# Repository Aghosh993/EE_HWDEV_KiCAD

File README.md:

# EE_HWDEV_KiCAD
Repository containing all KiCAD schematic, layout and project files for PCB schematic capture and layout projects

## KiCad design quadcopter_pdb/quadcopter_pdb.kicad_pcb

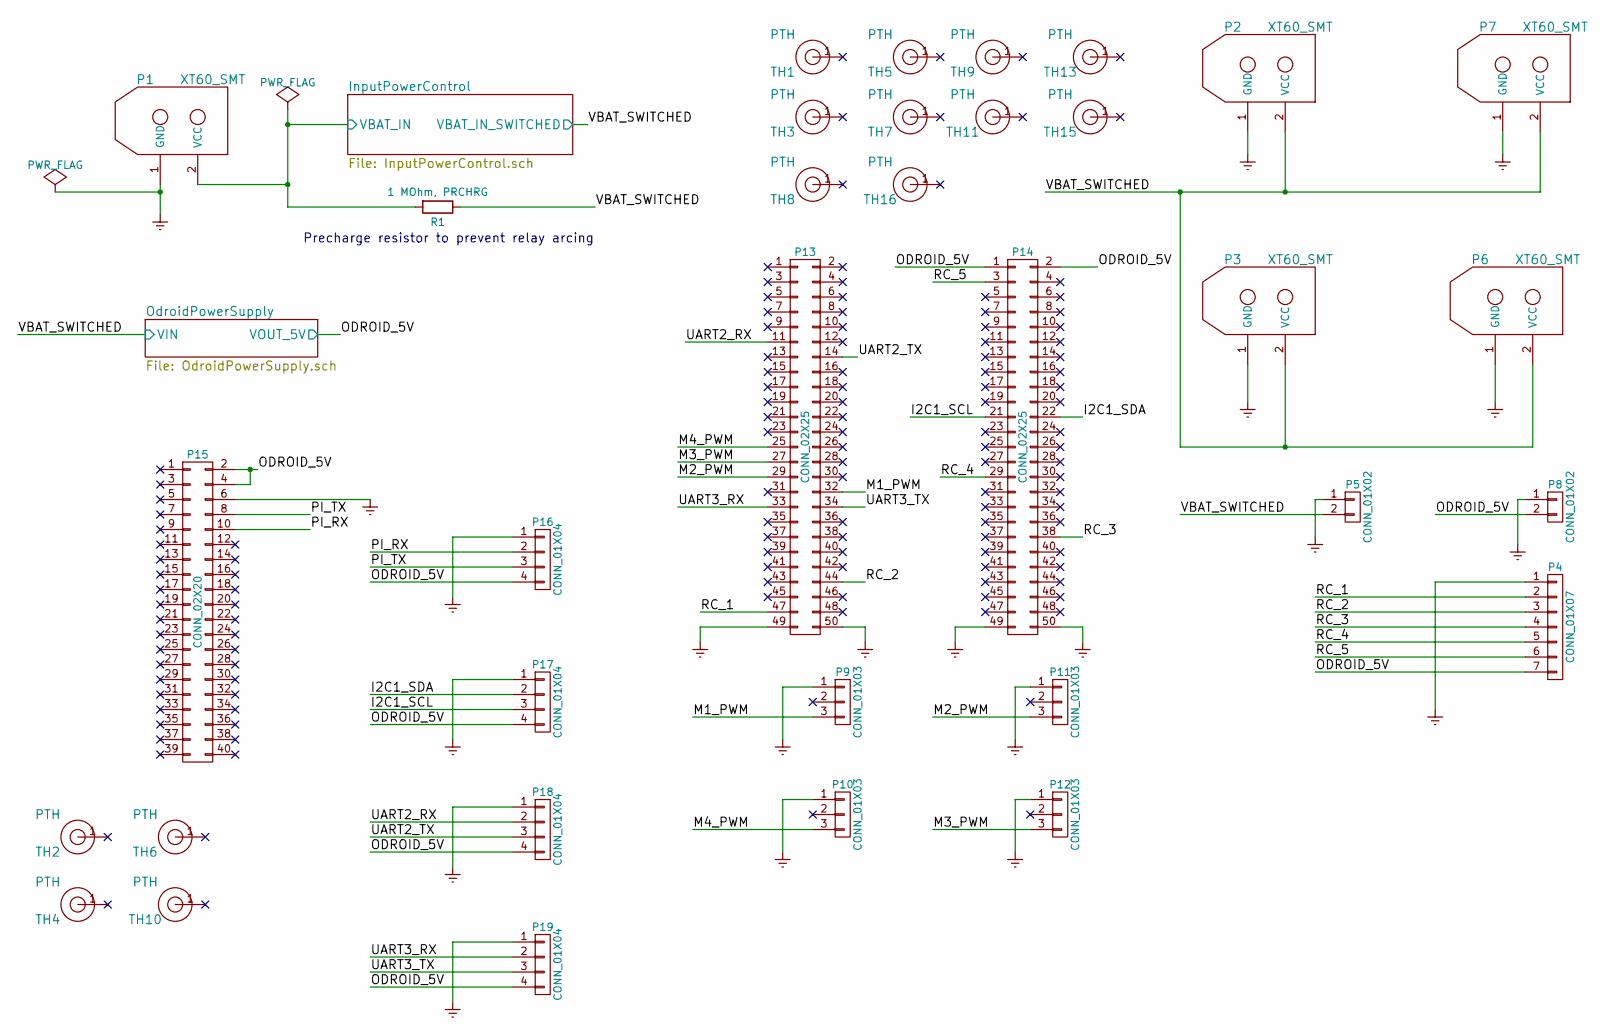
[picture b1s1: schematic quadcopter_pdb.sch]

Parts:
P1, P2, P3, P6, P7: XT60_SMT
P4: CONN_01X07; Pin_Header_Straight_1x07
P5, P8: CONN_01X02; Pin_Header_Angled_1x02
P9, P10, P11, P12: CONN_01X03; Pin_Header_Straight_1x03
P13, P14: CONN_02X25; Pin_Header_Straight_2x25
P15: CONN_02X20; Pin_Header_Straight_2x20
P16, P17, P18, P19: CONN_01X04; Pin_Header_Straight_1x04
R1: 1 MOhm, PRCHRG; R_0402
TH1, TH3, TH5, TH7, TH8, TH9, TH11, TH13, TH15, TH16: PTH
TH2, TH4, TH6, TH10: PTH; MountingHole_3mm

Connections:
/I2C1_SCL: P14.21, P17.3
/I2C1_SDA: P14.22, P17.2
/InputPowerControl/VBAT_IN: P1.2 (VCC), R1.2; also elsewhere on the board
/M1_PWM: P9.3, P13.32
/M2_PWM: P11.3, P13.29
/M3_PWM: P12.3, P13.27
/M4_PWM: P10.3, P13.25
/ODROID_5V: P4.7, P8.2, P14.1, P14.2, P15.2, P15.4, P16.4, P17.4, P18.4, P19.4; also elsewhere on the board
/PI_RX: P15.10, P16.2
/PI_TX: P15.8, P16.3
/RC_1: P4.2, P13.47
/RC_2: P4.3, P13.44
/RC_3: P4.4, P14.38
/RC_4: P4.5, P14.29
/RC_5: P4.6, P14.3
/UART2_RX: P13.11, P18.2
/UART2_TX: P13.14, P18.3
/UART3_RX: P13.33, P19.2
/UART3_TX: P13.34, P19.3
/VBAT_SWITCHED: P2.2 (VCC), P3.2 (VCC), P5.2, P6.2 (VCC), P7.2 (VCC), R1.1; also elsewhere on the board
Earth: P1.1 (GND), P2.1 (GND), P3.1 (GND), P4.1, P5.1, P6.1 (GND), P7.1 (GND), P8.1, P9.1, P10.1, P11.1, P12.1, P13.49, P13.50, P14.49, P14.50, P15.6, P16.1, P17.1, P18.1, P19.1; also elsewhere on the board

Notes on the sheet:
Precharge resistor to prevent relay arcing

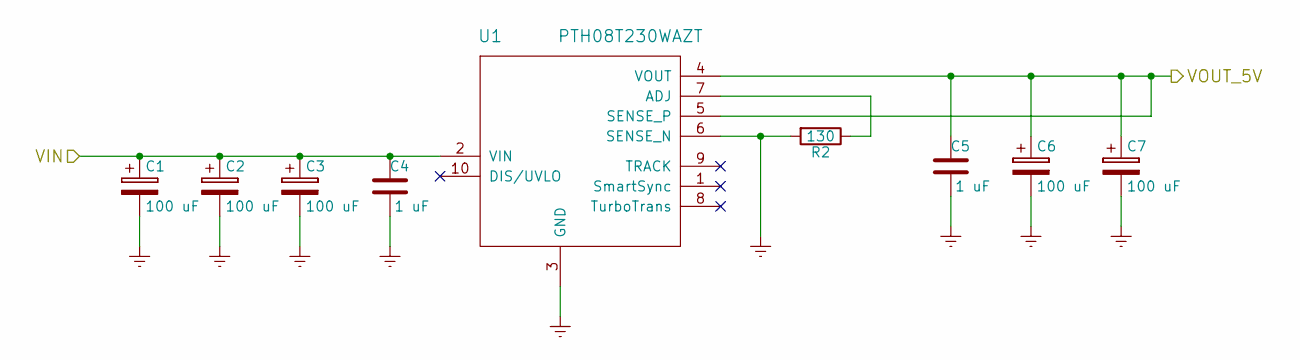
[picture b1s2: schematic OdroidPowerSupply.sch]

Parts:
C1, C2, C3, C6, C7: 100 uF; C_Radial_D6.3_L11.2_P2.5
C4, C5: 1 uF; C_0805_HandSoldering
R2: 130; R_0603_HandSoldering
U1: PTH08T230WAZT; PTH08T230WAZT_BCM

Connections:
/ODROID_5V: C5.2, C6.1, C7.1, U1.4 (VOUT), U1.5 (SENSE_P); also elsewhere on the board
/VBAT_SWITCHED: C1.1, C2.1, C3.1, C4.2, U1.2 (VIN); also elsewhere on the board
Earth: C1.2, C2.2, C3.2, C4.1, C5.1, C6.2, C7.2, R2.2, U1.3 (GND), U1.6 (SENSE_N); also elsewhere on the board
unnamed: R2.1, U1.7 (ADJ)

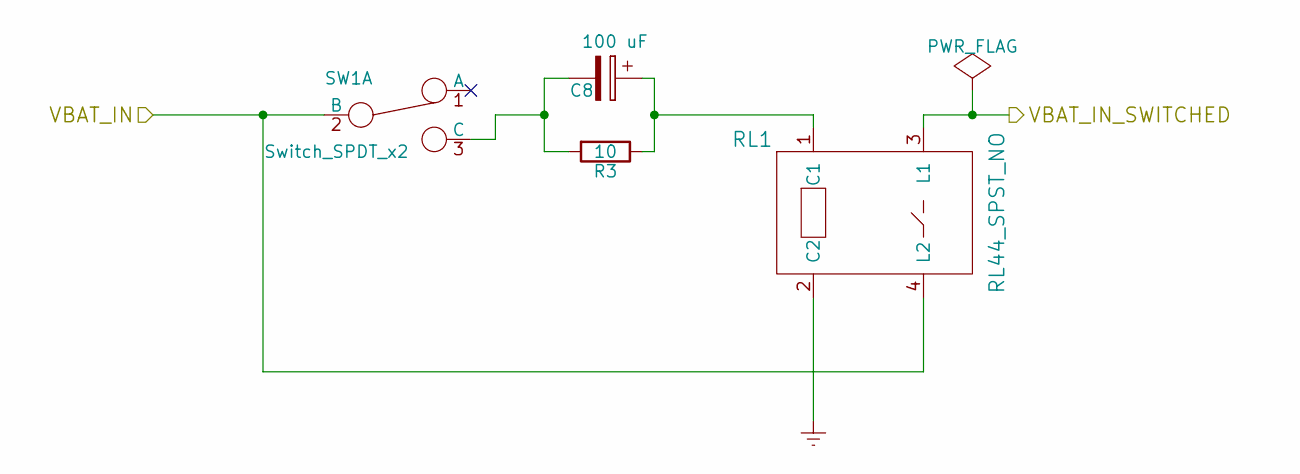
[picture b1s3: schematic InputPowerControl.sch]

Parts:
C8: 100 uF; C_Radial_D6.3_L11.2_P2.5
R3: 10; Resistor_Horizontal_RM10mm
RL1: RL44_SPST_NO; RELAY_RL44
SW1: Switch_SPDT_x2; SW_SPDT_ThroughHole

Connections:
/InputPowerControl/VBAT_IN: RL1.4 (L2), SW1.2 (B); also elsewhere on the board
/VBAT_SWITCHED: RL1.3 (L1); also elsewhere on the board
Earth: RL1.2 (C2); also elsewhere on the board
unnamed: C8.1, R3.1, RL1.1 (C1)
unnamed: C8.2, R3.2, SW1.3 (C)

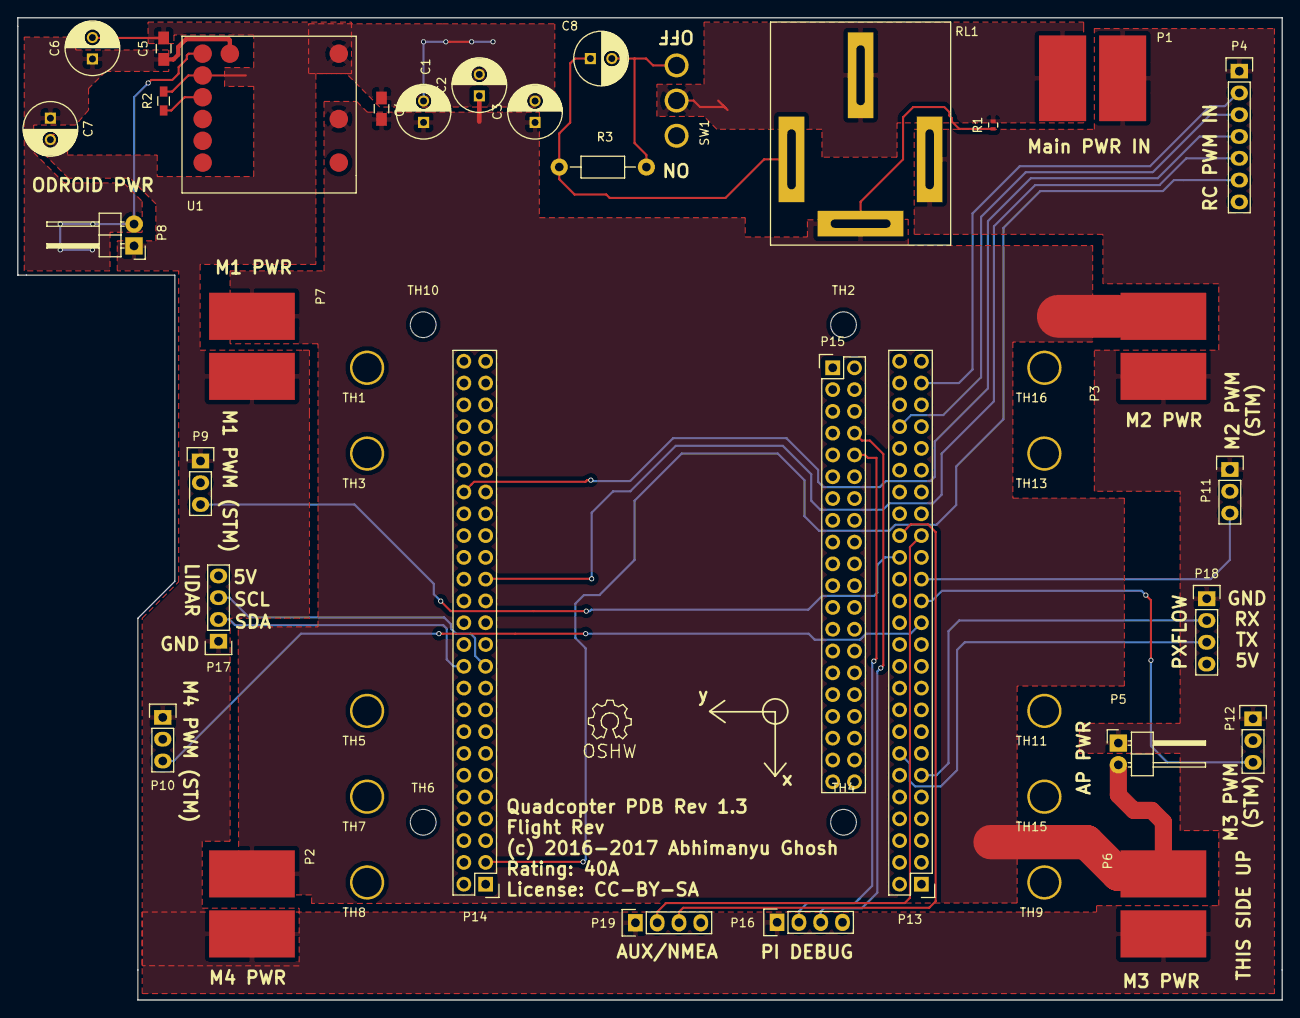
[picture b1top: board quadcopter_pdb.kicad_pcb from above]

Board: 2 copper layers, 147.4 x 114.5 mm, 47 parts (0 on the bottom side), 24 nets.

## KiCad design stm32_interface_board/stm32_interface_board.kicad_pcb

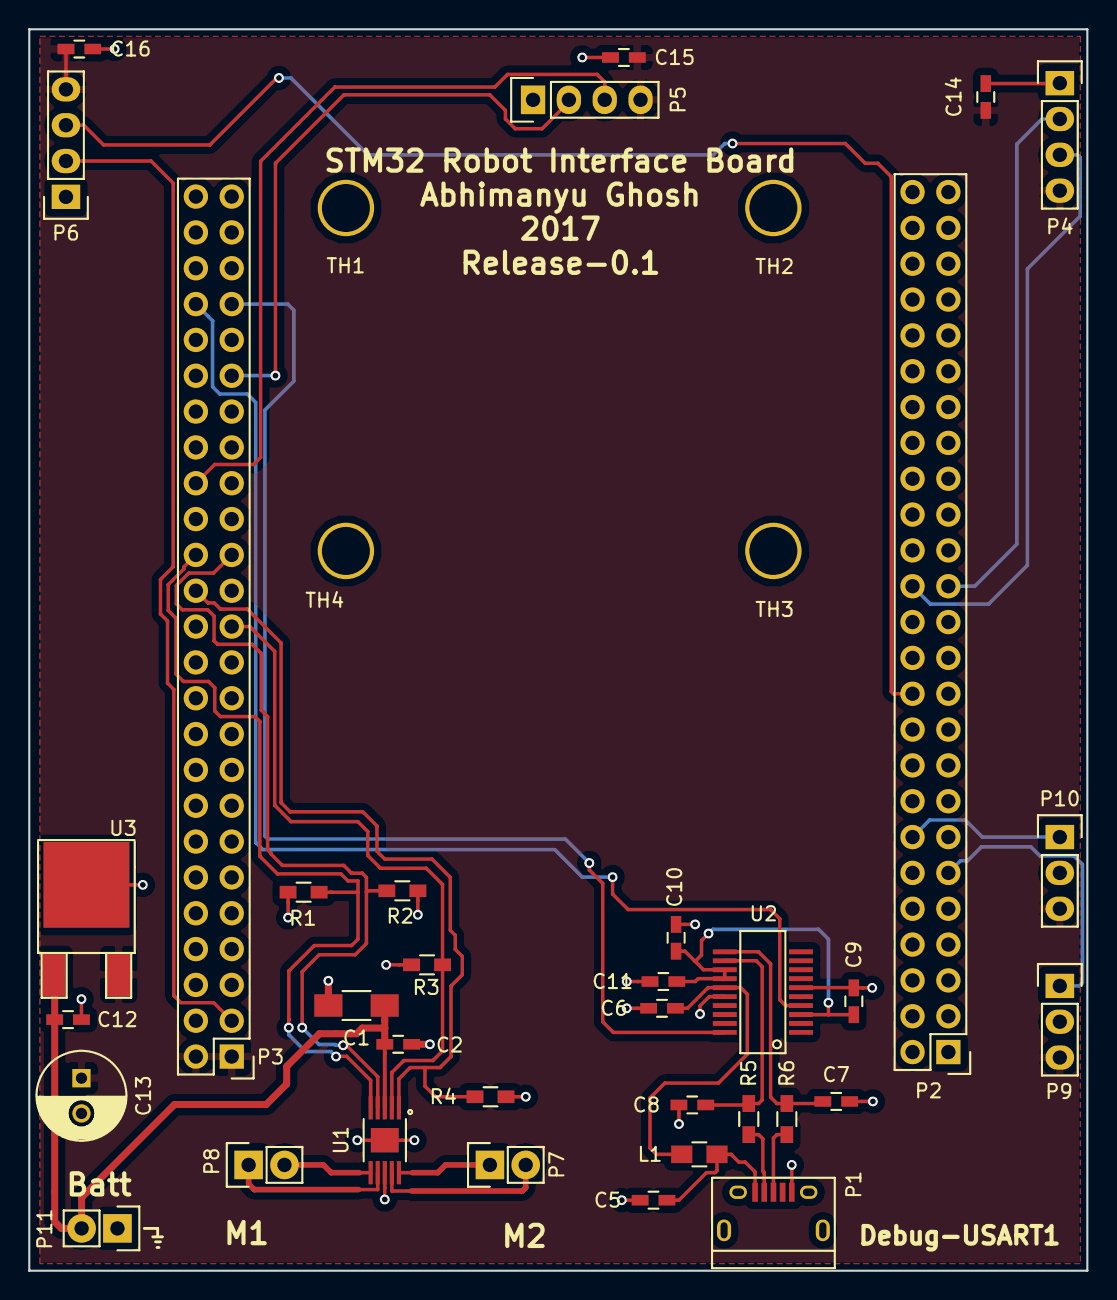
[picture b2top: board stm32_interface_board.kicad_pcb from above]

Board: 2 copper layers, 75.0 x 88.0 mm, 39 parts (0 on the bottom side), 28 nets.

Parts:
C1: 22 uF; C_1206_HandSoldering
C2, C5, C6, C9, C10, C11, C12, C14, C15, C16: 0.1 uF; C_0603_HandSoldering
C7, C8: 47 pF; C_0603_HandSoldering
C13: 2.2 uF; C_Radial_D6.3_L11.2_P2.5
L1: 40-Ohm Ferrite; C_0805_HandSoldering
P1: USB_OTG; USB_Micro-B
P2, P3: CONN_02X25; Pin_Header_Straight_2x25
P4, P5, P6: CONN_01X04; Pin_Header_Straight_1x04
P7, P8, P11: CONN_01X02; Pin_Header_Straight_1x02
P9, P10: CONN_01X03; Pin_Header_Straight_1x03
R1, R2, R3, R4: R; R_0603_HandSoldering
R5, R6: 27; R_0603_HandSoldering
TH1, TH2, TH3, TH4: PTH
U1: A3909; MSOP10-3x3-EP
U2: FT231XS; SSOP-20-8.66x3.91_0.635mm
U3: LF50ABDT-TR; TO-252-2Lead

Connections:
+5V: C13.1, C14.1, C15.1, C16.1, P3.1, P3.2, P4.4, P5.4, P6.4, P9.3, P10.3, U3.3
+BATT: C1.1, C2.1, C12.1, P11.2, U1.3, U3.1
/AIN0: P2.11, P9.1
/AIN1: P2.14, P10.1
/ECHO0: P2.27, P4.2
/ECHO1: P3.39, P5.2
/ECHO2: P3.3, P6.2
/M1_1: P3.28, R4.1, U1.1
/M1_2: P3.25, R3.1, U1.2
/M2_1: P3.29, R2.1, U1.4
/M2_2: P3.30, R1.1, U1.5
/MCU_RX: P3.43, U2.20
/MCU_TX: P3.44, U2.4
/MotorDriver/M1N: P7.2, U1.9
/MotorDriver/M1P: P7.1, U1.10
/MotorDriver/M2N: P8.2, U1.6
/MotorDriver/M2P: P8.1, U1.7
/TRIG0: P2.28, P4.3
/TRIG1: P3.34, P5.3
/TRIG2: P2.22, P6.3
/debugFTDI/USBD+: P1.3, R6.2
/debugFTDI/USBD-: P1.2, R5.2
/debugFTDI/USB_5V: C5.1, L1.2, P1.1
Earth: C1.2, C2.2, C5.2, C6.2, C7.2, C8.2, C9.2, C10.2, C11.2, C12.2, C13.2, C14.2, C15.2, C16.2, P1.5, P1.6, P2.49, P2.50, P3.49, P3.50, P4.1, P5.1, P6.1, P9.2, P10.2, P11.1, R1.2, R2.2, R3.2, R4.2, TH1.1, TH2.1, TH3.1, TH4.1, U1.8, U1.11, U2.6, U2.16, U3.2
unnamed: C6.1, L1.1, U2.15
unnamed: C7.1, R6.1, U2.11
unnamed: C8.1, R5.1, U2.12
unnamed: C9.1, C10.1, C11.1, U2.3, U2.13, U2.14

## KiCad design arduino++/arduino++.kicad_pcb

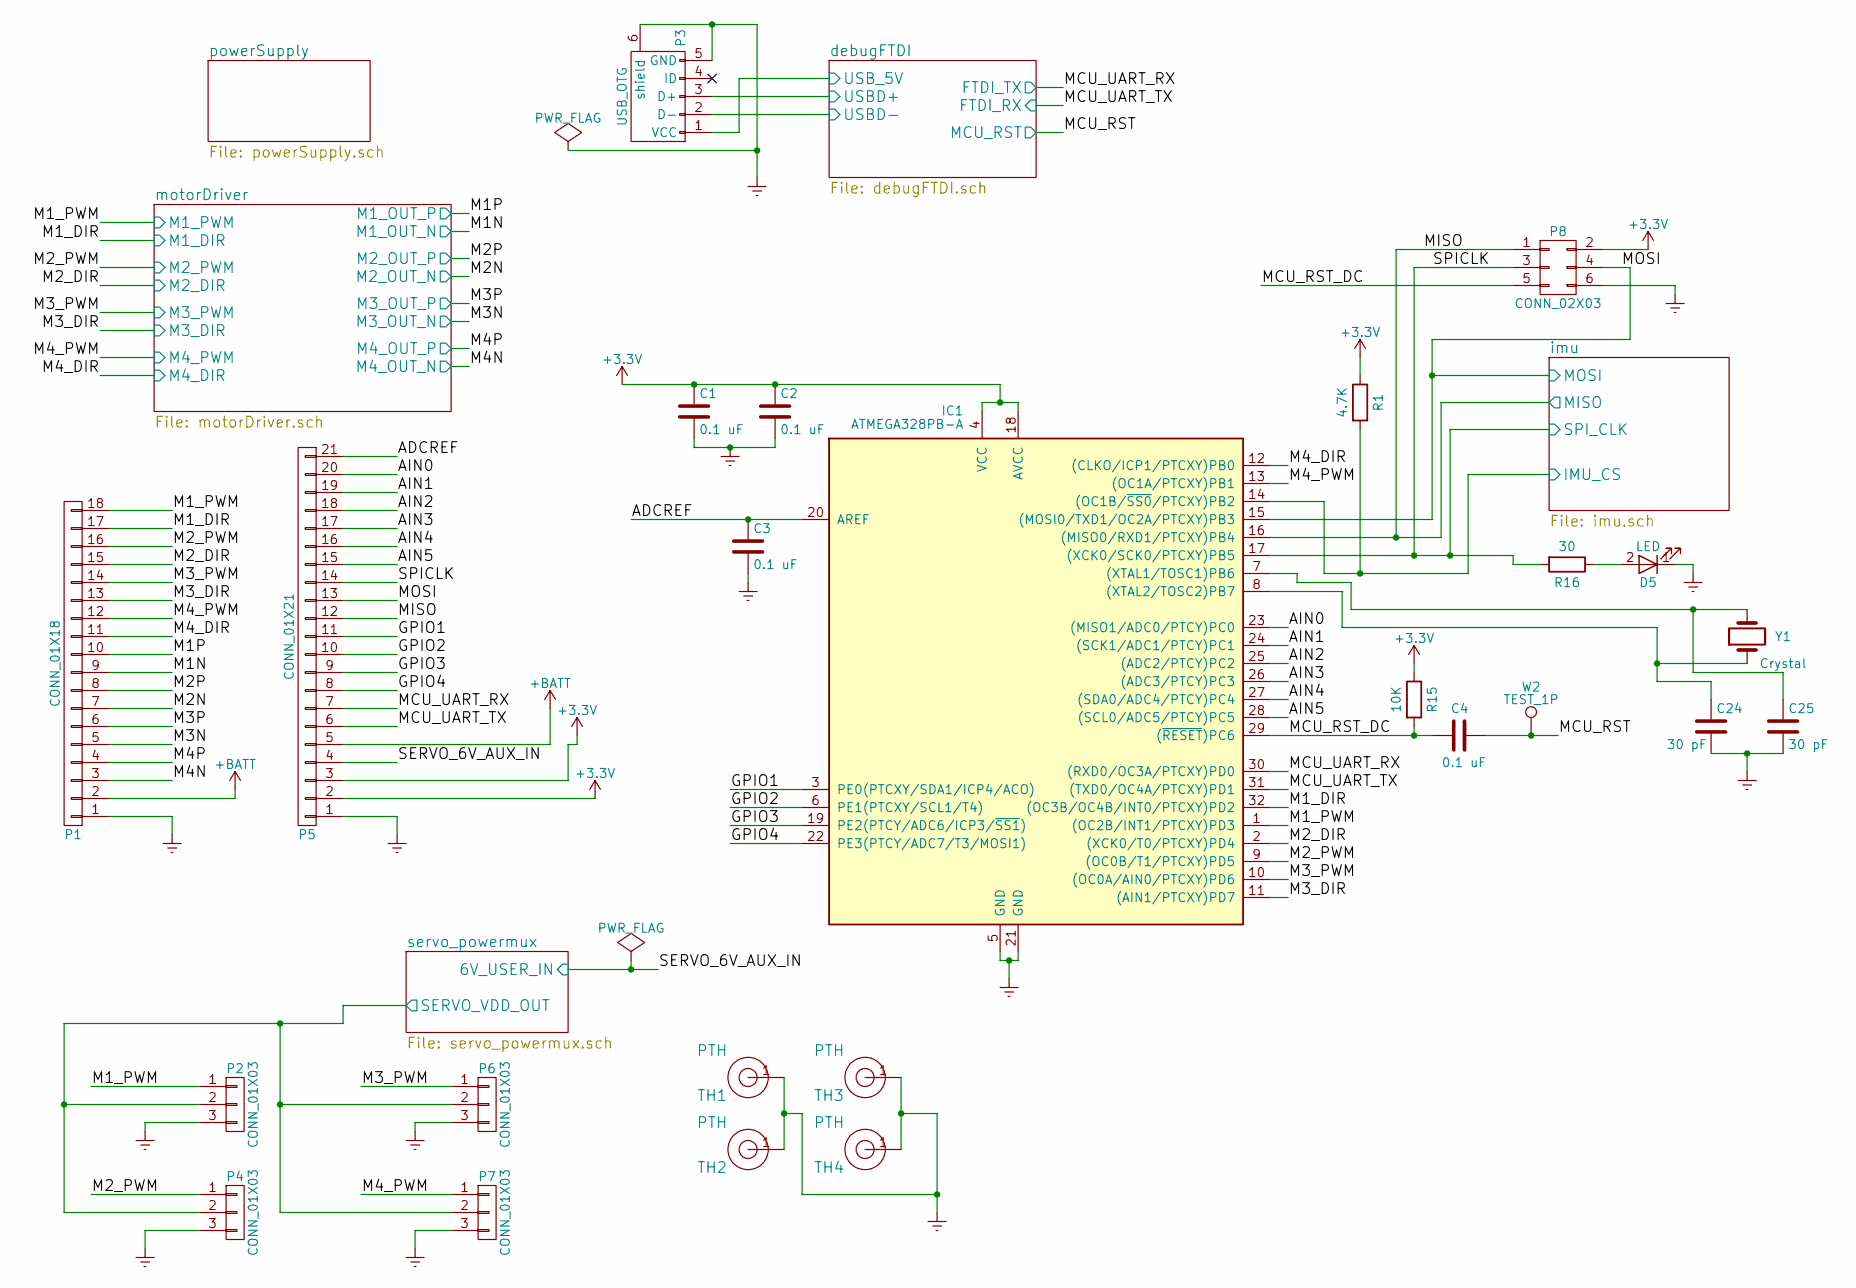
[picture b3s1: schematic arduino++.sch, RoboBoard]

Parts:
C1, C2, C3, C4: 0.1 uF; C_0402
C24, C25: 30 pF; C_0402
D5: LED; LED-0603
IC1: ATMEGA328PB-A; TQFP-32_7x7mm_Pitch0.8mm
P1: CONN_01X18; Pin_Header_Straight_1x18
P2, P4, P6, P7: CONN_01X03; Pin_Header_Straight_1x03
P3: USB_OTG; USB_Micro-B
P5: CONN_01X21; Pin_Header_Straight_1x21
P8: CONN_02X03; Pin_Header_Straight_2x03
R1: 4.7K; R_0402
R15: 10K; R_0603
R16: 30; R_0402
TH1, TH2, TH3, TH4: PTH
W2: TEST_1P; Measurement_Point_Round-SMD-Pad_Small
Y1: Crystal; Crystal_HC49-U_Vertical

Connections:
+3V3: C1.1, C2.1, IC1.4 (VCC), IC1.18 (AVCC), P5.2, P5.3, P8.2, R1.1, R15.1; also elsewhere on the board
+BATT: P1.2, P5.5; also elsewhere on the board
/ADCREF: C3.1, IC1.20 (AREF), P5.21
/AIN0: IC1.23 ((MISO1/ADC0/PTCY)PC0), P5.20
/AIN1: IC1.24 ((SCK1/ADC1/PTCY)PC1), P5.19
/AIN2: IC1.25 ((ADC2/PTCY)PC2), P5.18
/AIN3: IC1.26 ((ADC3/PTCY)PC3), P5.17
/AIN4: IC1.27 ((SDA0/ADC4/PTCY)PC4), P5.16
/AIN5: IC1.28 ((SCL0/ADC5/PTCY)PC5), P5.15
/GPIO1: IC1.3 (PE0(PTCXY/SDA1/ICP4/ACO)), P5.11
/GPIO2: IC1.6 (PE1(PTCXY/SCL1/T4)), P5.10
/GPIO3: IC1.19 (PE2(PTCY/ADC6/ICP3/~SS1~)), P5.9
/GPIO4: IC1.22 (PE3(PTCY/ADC7/T3/MOSI1)), P5.8
/M1N: P1.9; also elsewhere on the board
/M1P: P1.10; also elsewhere on the board
/M1_DIR: IC1.32 ((OC3B/OC4B/INT0/PTCXY)PD2), P1.17; also elsewhere on the board
/M1_PWM: IC1.1 ((OC2B/INT1/PTCXY)PD3), P1.18, P2.1; also elsewhere on the board
/M2N: P1.7; also elsewhere on the board
/M2P: P1.8; also elsewhere on the board
/M2_DIR: IC1.2 ((XCK0/T0/PTCXY)PD4), P1.15; also elsewhere on the board
/M2_PWM: IC1.9 ((OC0B/T1/PTCXY)PD5), P1.16, P4.1; also elsewhere on the board
/M3N: P1.5; also elsewhere on the board
/M3P: P1.6; also elsewhere on the board
/M3_DIR: IC1.11 ((AIN1/PTCXY)PD7), P1.13; also elsewhere on the board
/M3_PWM: IC1.10 ((OC0A/AIN0/PTCXY)PD6), P1.14, P6.1; also elsewhere on the board
/M4N: P1.3; also elsewhere on the board
/M4P: P1.4; also elsewhere on the board
/M4_DIR: IC1.12 ((CLKO/ICP1/PTCXY)PB0), P1.11; also elsewhere on the board
/M4_PWM: IC1.13 ((OC1A/PTCXY)PB1), P1.12, P7.1; also elsewhere on the board
/MCU_RST: C4.1, W2.1; also elsewhere on the board
/MCU_RST_DC: C4.2, IC1.29 ((~RESET~)PC6), P8.5, R15.2
/MCU_UART_RX: IC1.30 ((RXD0/OC3A/PTCXY)PD0), P5.7; also elsewhere on the board
/MCU_UART_TX: IC1.31 ((TXD0/OC4A/PTCXY)PD1), P5.6; also elsewhere on the board
/MISO: IC1.16 ((MISO0/RXD1/PTCXY)PB4), P5.12, P8.1; also elsewhere on the board
/MOSI: IC1.15 ((MOSI0/TXD1/OC2A/PTCXY)PB3), P5.13, P8.4; also elsewhere on the board
/SERVO_6V_AUX_IN: P5.4; also elsewhere on the board
/SPICLK: IC1.17 ((XCK0/SCK0/PTCXY)PB5), P5.14, P8.3, R16.2; also elsewhere on the board
/debugFTDI/USBD+: P3.3 (D+); also elsewhere on the board
/debugFTDI/USBD-: P3.2 (D-); also elsewhere on the board
/debugFTDI/USB_5V: P3.1 (VCC); also elsewhere on the board
/imu/IMU_CS: IC1.14 ((OC1B/~SS0~/PTCXY)PB2), R1.2; also elsewhere on the board
/servo_powermux/SERVO_VDD_OUT: P2.2, P4.2, P6.2, P7.2; also elsewhere on the board
Earth: C1.2, C2.2, C3.2, C24.2, C25.2, D5.1 (K), IC1.5 (GND), IC1.21 (GND), P1.1, P2.3, P3.5 (GND), P3.6 (shield), P4.3, P5.1, P6.3, P7.3, P8.6, TH1.1, TH2.1, TH3.1, TH4.1; also elsewhere on the board
unnamed: C24.1, IC1.8 ((XTAL2/TOSC2)PB7), Y1.1
unnamed: C25.1, IC1.7 ((XTAL1/TOSC1)PB6), Y1.2
unnamed: D5.2 (A), R16.1

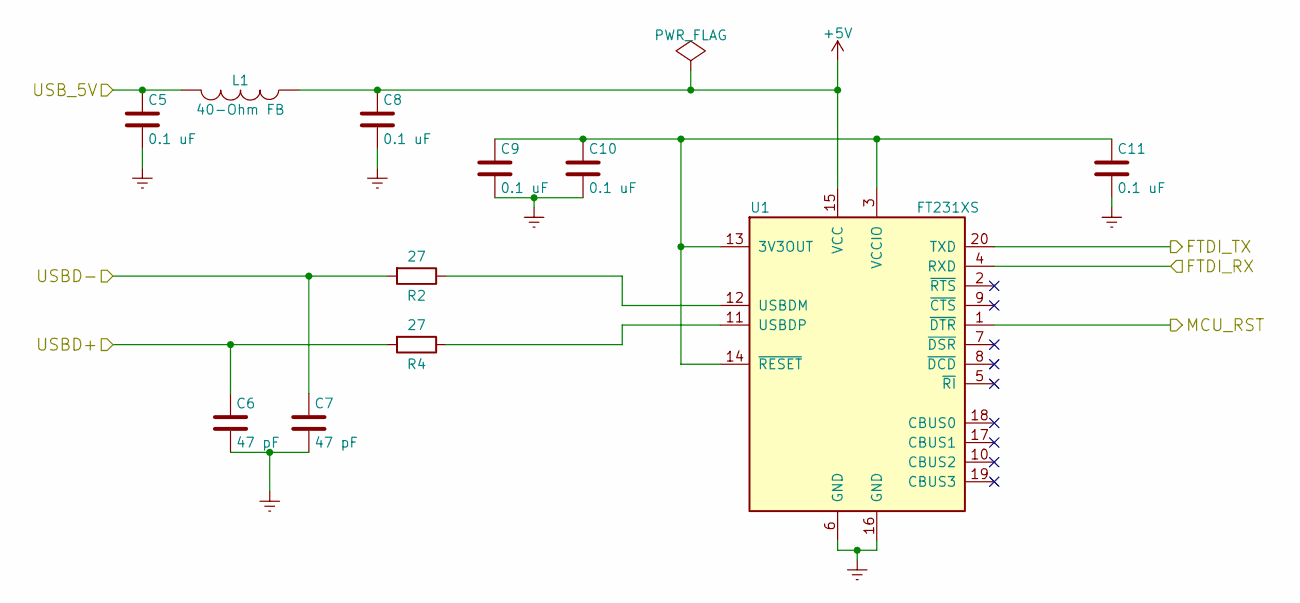
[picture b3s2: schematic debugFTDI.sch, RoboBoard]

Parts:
C5, C8, C9, C10, C11: 0.1 uF; C_0402
C6, C7: 47 pF; C_0603
L1: 40-Ohm FB; C_0805_HandSoldering
R2, R4: 27; R_0603
U1: FT231XS; SSOP-20-8.66x3.91_0.635mm

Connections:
+5V: C8.1, L1.1, U1.15 (VCC); also elsewhere on the board
/MCU_RST: U1.1 (~DTR); also elsewhere on the board
/MCU_UART_RX: U1.20 (TXD); also elsewhere on the board
/MCU_UART_TX: U1.4 (RXD); also elsewhere on the board
/debugFTDI/USBD+: C6.1, R4.2; also elsewhere on the board
/debugFTDI/USBD-: C7.1, R2.2; also elsewhere on the board
/debugFTDI/USB_5V: C5.1, L1.2; also elsewhere on the board
Earth: C5.2, C6.2, C7.2, C8.2, C9.2, C10.2, C11.2, U1.6 (GND), U1.16 (GND); also elsewhere on the board
unnamed: C9.1, C10.1, C11.1, U1.3 (VCCIO), U1.13 (3V3OUT), U1.14 (~RESET)
unnamed: R2.1, U1.12 (USBDM)
unnamed: R4.1, U1.11 (USBDP)

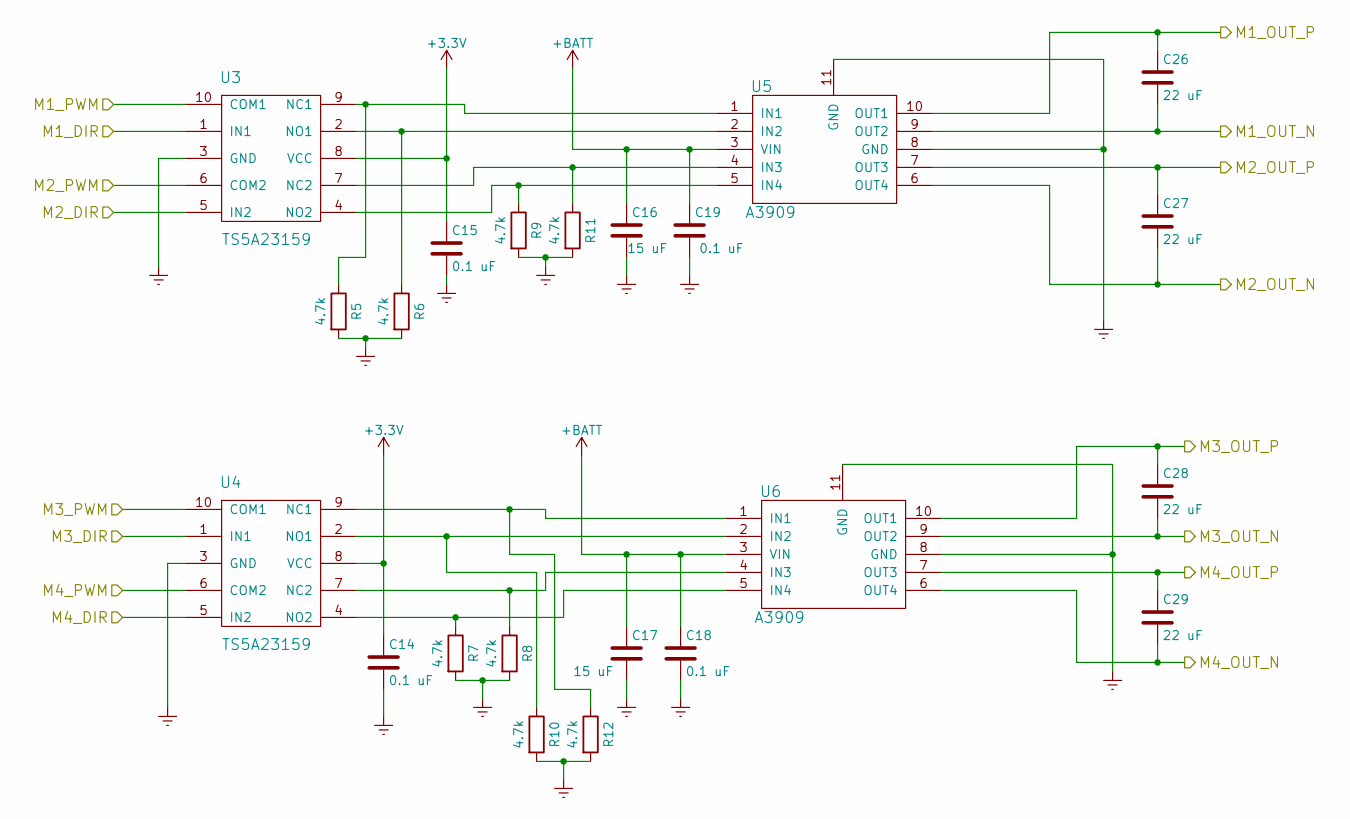
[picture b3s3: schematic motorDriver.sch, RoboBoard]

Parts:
C14, C15, C18, C19: 0.1 uF; C_0402
C16, C17: 15 uF; C_0805_HandSoldering
C26, C27, C28, C29: 22 uF; C_1206
R5, R6, R7, R8, R9, R10, R11, R12: 4.7k; R_0402
U3, U4: TS5A23159; TSSOP-10_3x3mm_Pitch0.5mm
U5, U6: A3909; MSOP10-3x3-EP

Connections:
+3V3: C14.1, C15.1, U3.8 (VCC), U4.8 (VCC); also elsewhere on the board
+BATT: C16.1, C17.1, C18.1, C19.1, U5.3 (VIN), U6.3 (VIN); also elsewhere on the board
/M1N: C26.2, U5.9 (OUT2); also elsewhere on the board
/M1P: C26.1, U5.10 (OUT1); also elsewhere on the board
/M1_DIR: U3.1 (IN1); also elsewhere on the board
/M1_PWM: U3.10 (COM1); also elsewhere on the board
/M2N: C27.2, U5.6 (OUT4); also elsewhere on the board
/M2P: C27.1, U5.7 (OUT3); also elsewhere on the board
/M2_DIR: U3.5 (IN2); also elsewhere on the board
/M2_PWM: U3.6 (COM2); also elsewhere on the board
/M3N: C28.2, U6.9 (OUT2); also elsewhere on the board
/M3P: C28.1, U6.10 (OUT1); also elsewhere on the board
/M3_DIR: U4.1 (IN1); also elsewhere on the board
/M3_PWM: U4.10 (COM1); also elsewhere on the board
/M4N: C29.2, U6.6 (OUT4); also elsewhere on the board
/M4P: C29.1, U6.7 (OUT3); also elsewhere on the board
/M4_DIR: U4.5 (IN2); also elsewhere on the board
/M4_PWM: U4.6 (COM2); also elsewhere on the board
Earth: C14.2, C15.2, C16.2, C17.2, C18.2, C19.2, R5.2, R6.2, R7.2, R8.2, R9.2, R10.2, R11.2, R12.2, U3.3 (GND), U4.3 (GND), U5.8 (GND), U5.11 (GND), U6.8 (GND), U6.11 (GND); also elsewhere on the board
unnamed: R5.1, U3.9 (NC1), U5.1 (IN1)
unnamed: R6.1, U3.2 (NO1), U5.2 (IN2)
unnamed: R7.1, U4.4 (NO2), U6.5 (IN4)
unnamed: R8.1, U4.7 (NC2), U6.4 (IN3)
unnamed: R9.1, U3.4 (NO2), U5.5 (IN4)
unnamed: R10.1, U4.2 (NO1), U6.2 (IN2)
unnamed: R11.1, U3.7 (NC2), U5.4 (IN3)
unnamed: R12.1, U4.9 (NC1), U6.1 (IN1)

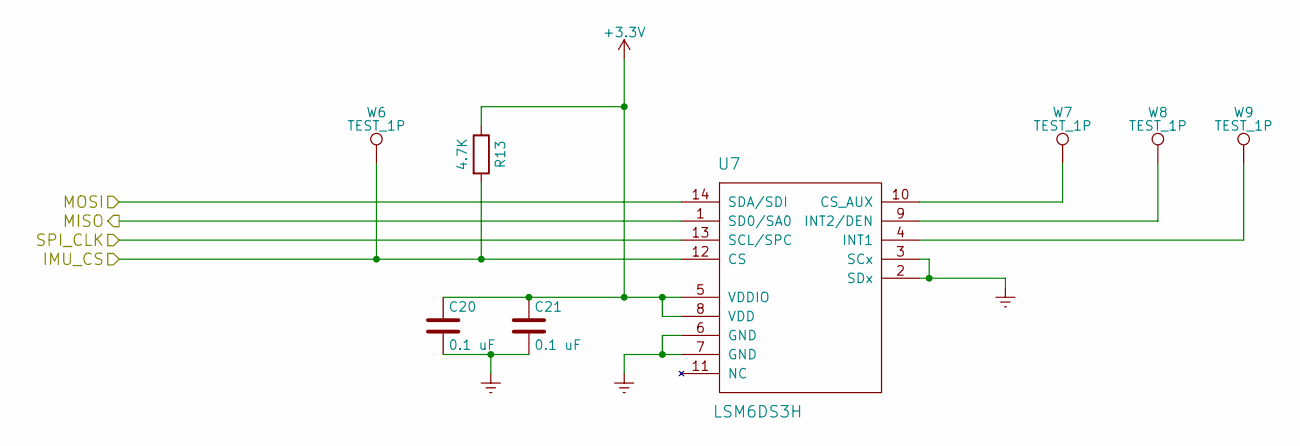
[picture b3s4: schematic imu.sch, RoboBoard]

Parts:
C20, C21: 0.1 uF; C_0402
R13: 4.7K; R_0402
U7: LSM6DS3H; LCC-14
W6, W7, W8, W9: TEST_1P; Measurement_Point_Round-SMD-Pad_Small

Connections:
+3V3: C20.1, C21.1, R13.1, U7.5 (VDDIO), U7.8 (VDD); also elsewhere on the board
/MISO: U7.1 (SD0/SA0); also elsewhere on the board
/MOSI: U7.14 (SDA/SDI); also elsewhere on the board
/SPICLK: U7.13 (SCL/SPC); also elsewhere on the board
/imu/IMU_CS: R13.2, U7.12 (CS), W6.1; also elsewhere on the board
Earth: C20.2, C21.2, U7.2 (SDx), U7.3 (SCx), U7.6 (GND), U7.7 (GND); also elsewhere on the board
unnamed: U7.4 (INT1), W9.1
unnamed: U7.9 (INT2/DEN), W8.1
unnamed: U7.10 (CS_AUX), W7.1

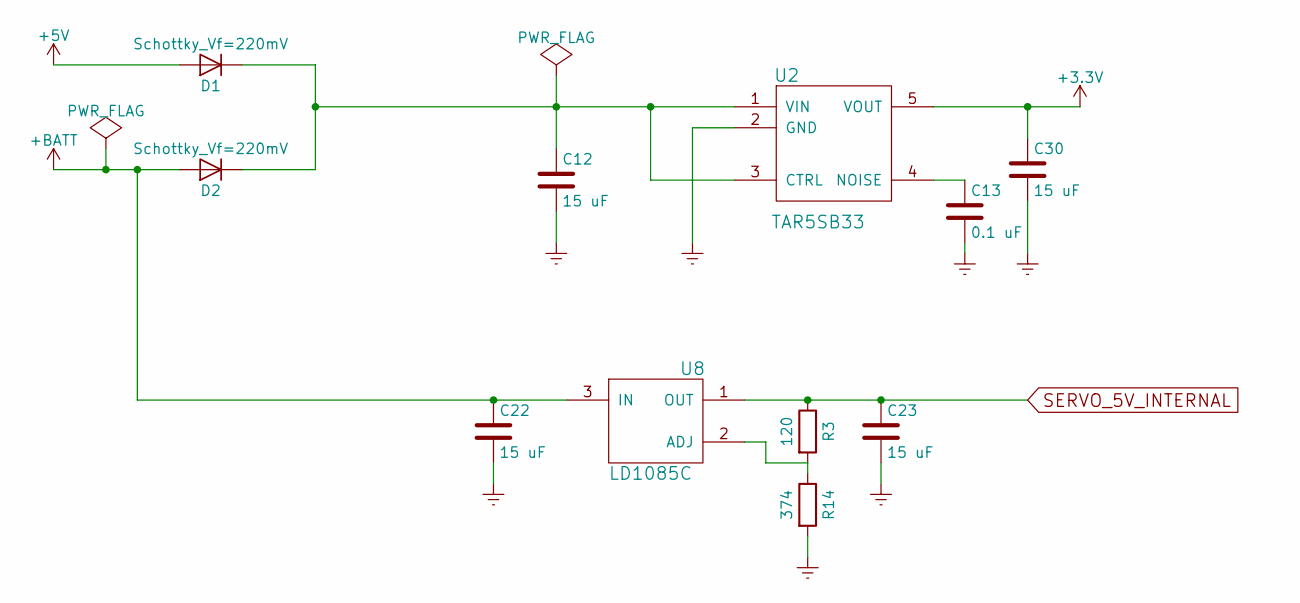
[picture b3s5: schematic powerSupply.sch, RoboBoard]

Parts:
C12, C22, C23, C30: 15 uF; C_0805_HandSoldering
C13: 0.1 uF; C_0402
D1, D2: Schottky_Vf=220mV; SOD-882
R3: 120; R_0603
R14: 374; R_0603
U2: TAR5SB33; SC-74A_SOT23-5
U8: LD1085C; DPAK

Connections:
+3V3: C30.1, U2.5 (VOUT); also elsewhere on the board
+5V: D1.2 (A); also elsewhere on the board
+BATT: C22.1, D2.2 (A), U8.3 (IN); also elsewhere on the board
Earth: C12.2, C13.2, C22.2, C23.2, C30.2, R14.2, U2.2 (GND); also elsewhere on the board
unnamed: C12.1, D1.1 (K), D2.1 (K), U2.1 (VIN), U2.3 (CTRL)
unnamed: C13.1, U2.4 (NOISE)
unnamed: R3.2, R14.1, U8.2 (ADJ)
SERVO_5V_INTERNAL: C23.1, R3.1, U8.1 (OUT); also elsewhere on the board

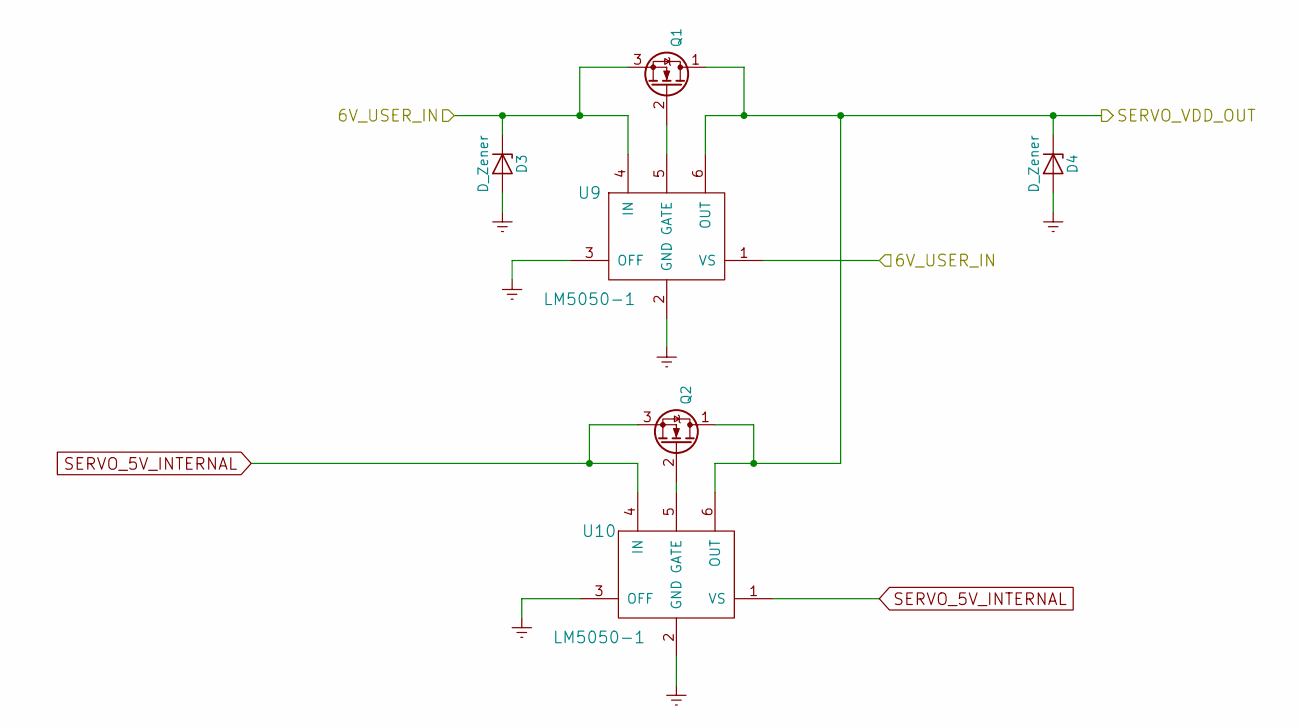
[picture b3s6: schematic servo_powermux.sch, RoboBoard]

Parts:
D3, D4: D_Zener; DO-214AA
Q1, Q2: Q_NMOS_DGS; SOT2-3_FET
U9, U10: LM5050-1; SOT-23-6-SC70

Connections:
/SERVO_6V_AUX_IN: D3.1 (K), Q1.3 (S), U9.1 (VS), U9.4 (IN); also elsewhere on the board
/servo_powermux/SERVO_VDD_OUT: D4.1 (K), Q1.1 (D), Q2.1 (D), U9.6 (OUT), U10.6 (OUT); also elsewhere on the board
Earth: D3.2 (A), D4.2 (A), U9.2 (GND), U9.3 (OFF), U10.2 (GND), U10.3 (OFF); also elsewhere on the board
unnamed: Q1.2 (G), U9.5 (GATE)
unnamed: Q2.2 (G), U10.5 (GATE)
SERVO_5V_INTERNAL: Q2.3 (S), U10.1 (VS), U10.4 (IN); also elsewhere on the board

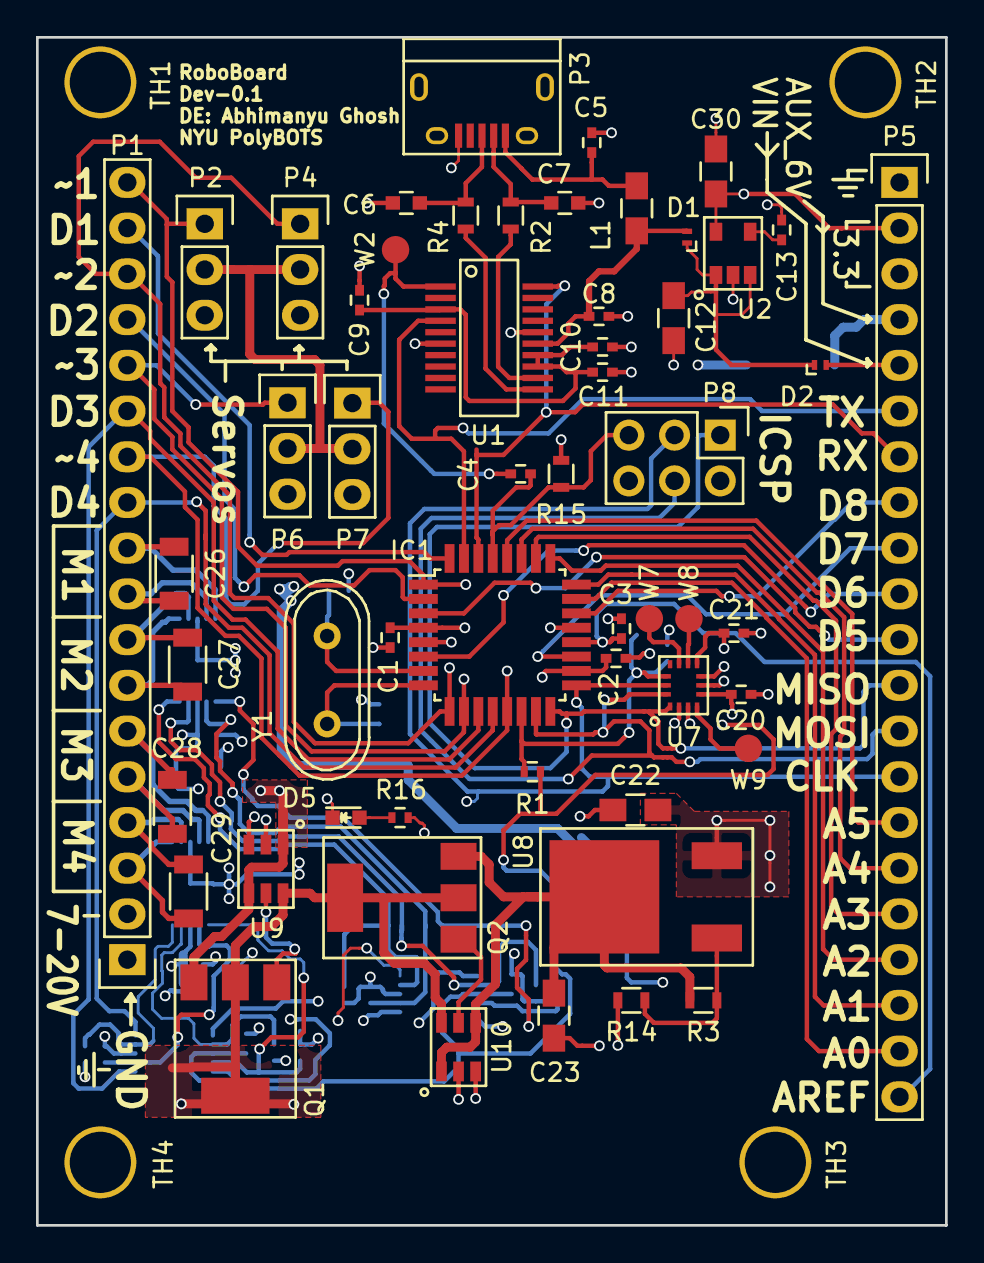
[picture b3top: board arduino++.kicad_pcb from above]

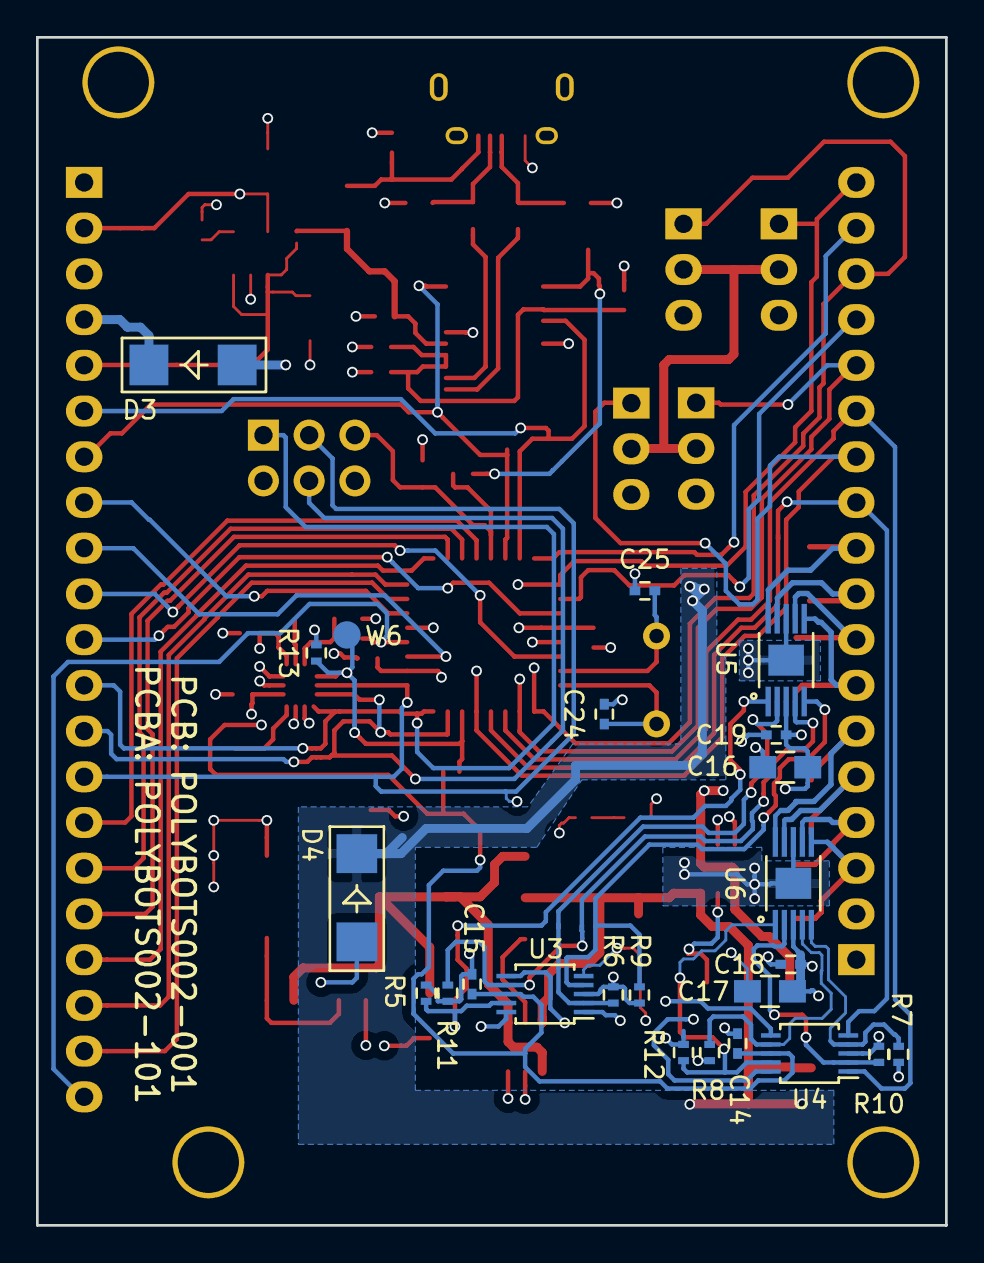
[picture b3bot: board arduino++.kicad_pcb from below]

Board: 4 copper layers, 50.5 x 66.0 mm, 83 parts (24 on the bottom side), 67 nets.

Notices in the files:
quadcopter_pdb/quadcopter_pdb.kicad_pcb:
(c) 2016-2017 Abhimanyu Ghosh
License: CC-BY-SA
